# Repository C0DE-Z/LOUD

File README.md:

# Loud REV 1

A open source analog Video glitcher 

- Uses Karl Klomps Dirty Mixer
- Audio Reacitve Effects

- Check code branch for Source code,

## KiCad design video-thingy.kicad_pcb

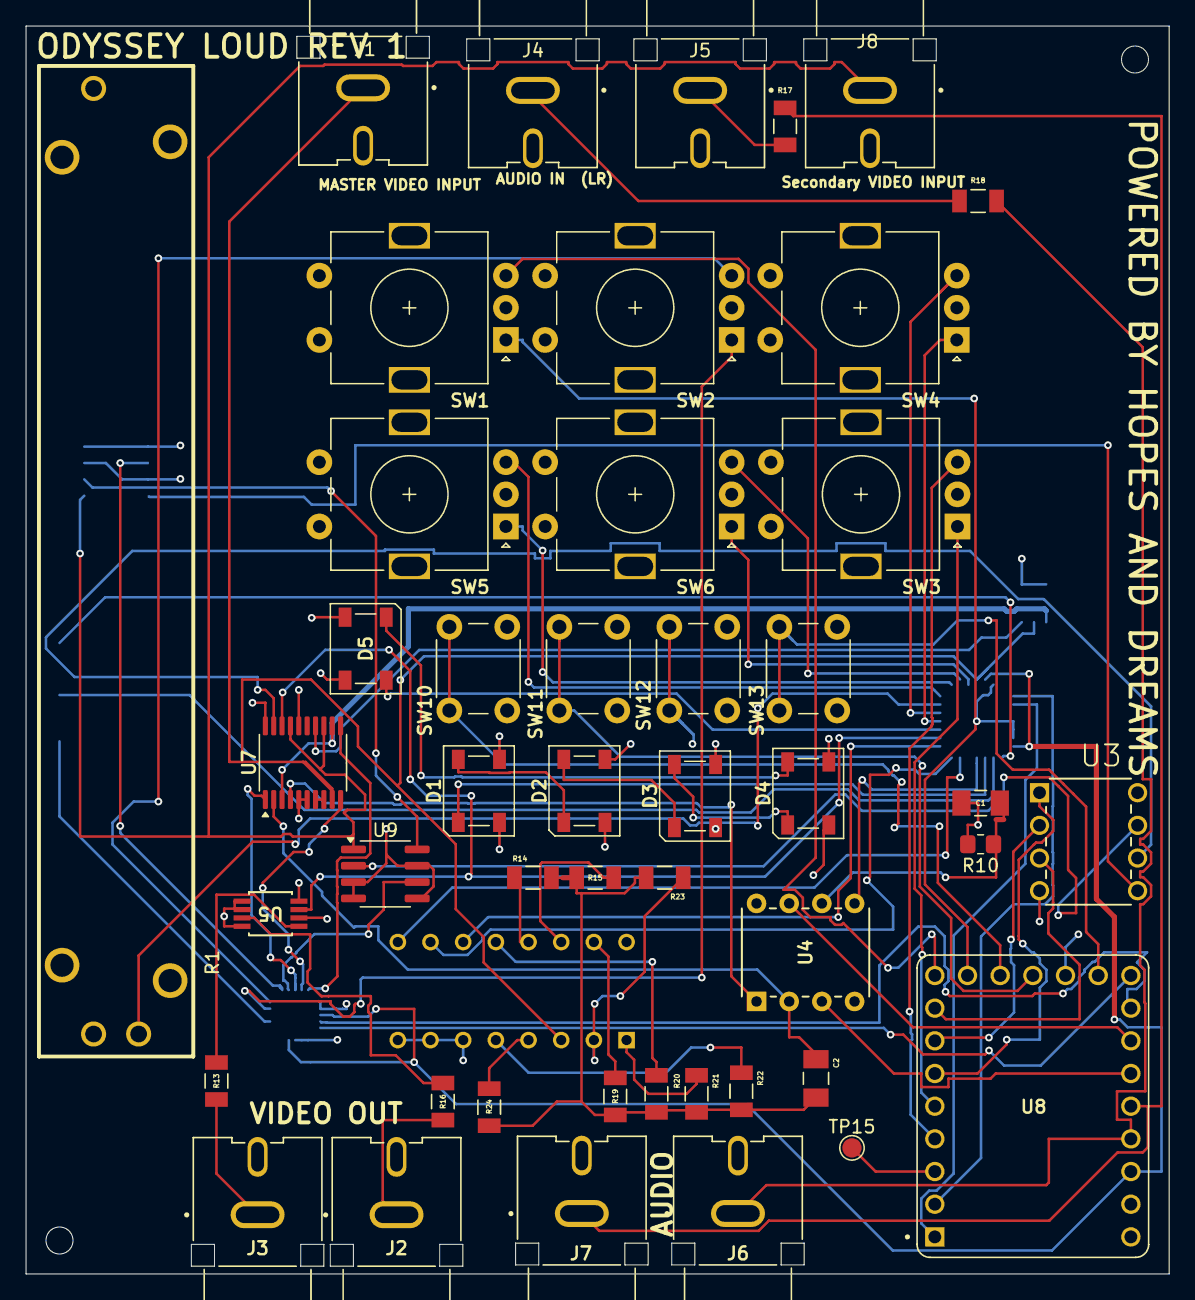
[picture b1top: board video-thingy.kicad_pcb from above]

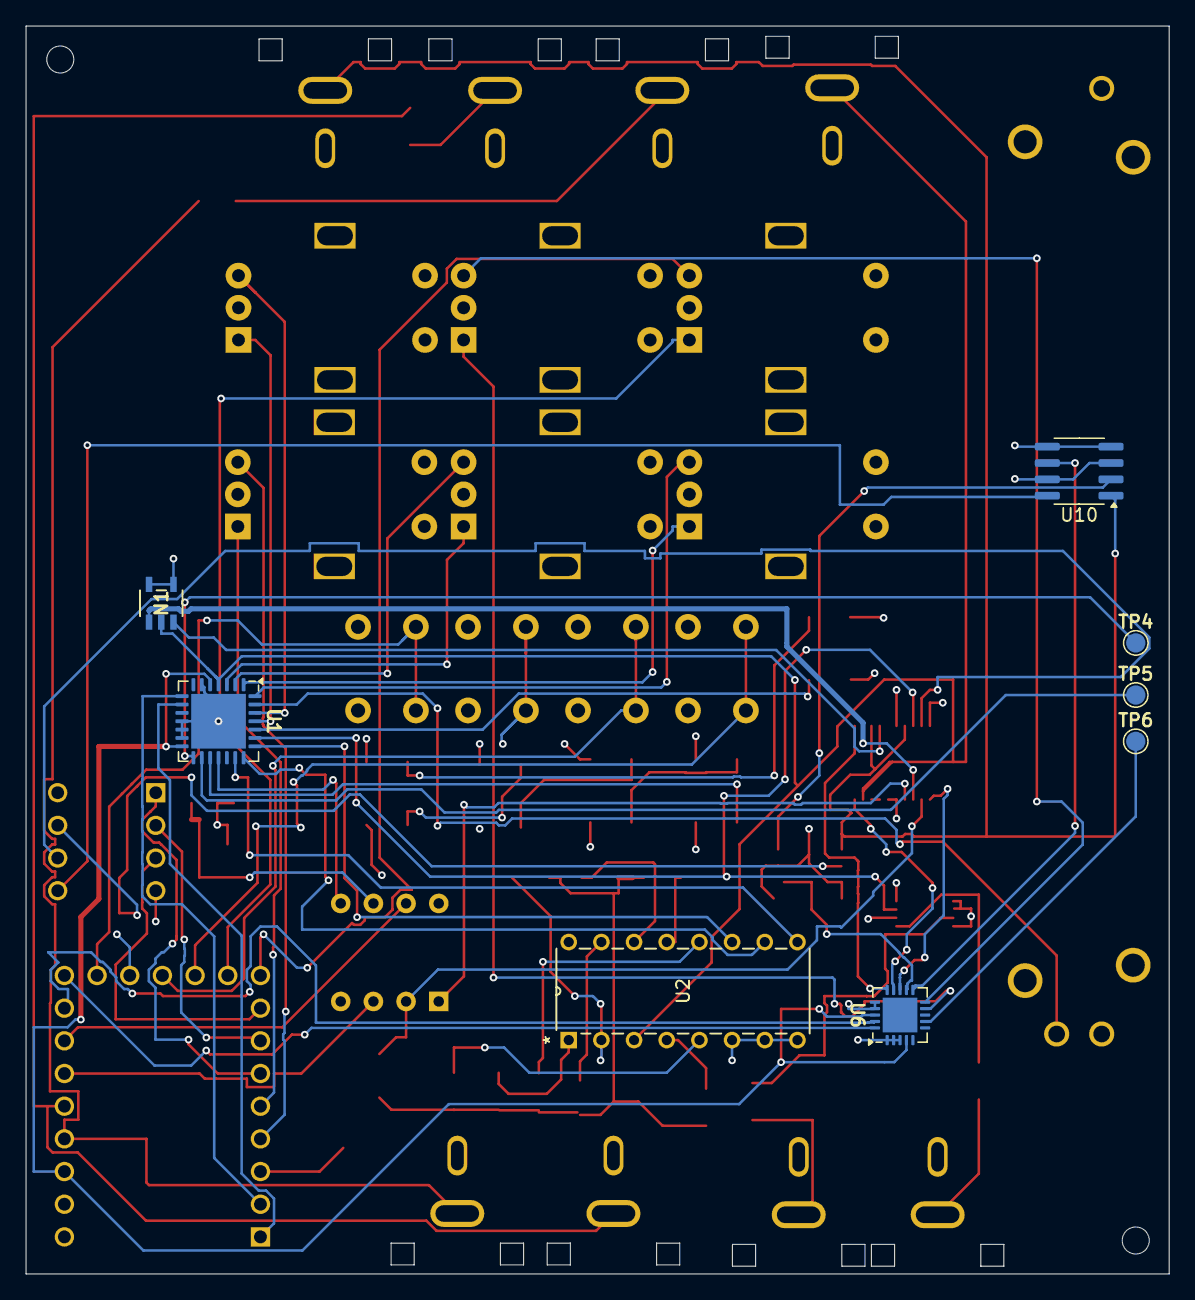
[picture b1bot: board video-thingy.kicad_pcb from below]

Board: 4 copper layers, 88.9 x 97.0 mm, 56 parts (8 on the bottom side), 74 nets.

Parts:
C1, C2: 0.1uF_0603_16V; CAPC3316X140N
D1, D2, D3, D4, D5: NeoPixel_THT; LED_Inolux_IN-PI554FCH_PLCC4_5.0x5.0mm_P3.2mm
J1, J2, J3, J4, J5, J6, J7, J8: RCJ-041; CUI_RCJ-041
MOUNT, MOUNT2: MountingHole_2.1mm
N1: DBV5-M
R1: PTA6043-2015DP-B103
R10: 680k; R_0805_2012Metric_Pad1.20x1.40mm_HandSolder
R13, R14, R15, R16, R17, R18, R19, R20, R21, R22, R23, R24: CRCW120675R0FKEAHP; RESC3116X65N
SW1, SW2, SW3, SW4, SW5, SW6: RotaryEncoder; RotaryEncoder_Alps_EC11E-Switch_Vertical_H20mm
SW10, SW11, SW12, SW13: Push_Button; SW_PUSH_6mm
TP4, TP5, TP6, TP15: TestPoint; TestPoint_Pad_D1.5mm
U1: MCP23017_ML; QFN-28-1EP_6x6mm_P0.65mm_EP4.25x4.25mm
U2: CD4051B; N16
U3: MCP41010; DIP254P762X432-8
U4: LM1881N; N08E_TEX
U5: MAX4392EUA_T; 21-0036_U8&plus_1_MXM
U6: MCP23008-xML; QFN-20-1EP_4x4mm_P0.5mm_EP2.7x2.7mm
U7: ADG734; TSSOP-20_4.4x6.5mm_P0.65mm
U8: RP2040-ZERO; MODULE_RP2040-ZERO
U9, U10: ADG419BR; SOIC-8_3.9x4.9mm_P1.27mm

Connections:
+3.3V: U1.5 (VDD), U1.14 (~RESET), U6.4 (~RESET), U6.18 (VDD), U8.21 (3V3)
A: SW4.A, U1.25 (GPB0)
A2: SW2.A, U6.9 (GP0)
A3: SW3.A, U8.5 (GP4)
A5: SW5.A, U1.1 (GPB4)
A6: SW6.A, U1.3 (GPB6)
AnalogL: J6.1, R18.1, U8.20 (GP29)
AnalogR: J7.1, R17.1, U8.19 (GP28)
AudioLIN: J4.1, R18.2
AudioRIN: J5.1, R17.2
B: SW4.B, U1.26 (GPB1)
B1: SW1.B, U8.9 (GP8)
B2: SW2.B, U6.10 (GP1)
B3: SW3.B, U8.4 (GP3)
B5: SW5.B, U1.28 (GPB3)
B6: SW6.B, U1.2 (GPB5)
BPOUT: U1.18 (GPA1), U4.5 (BPOUT)
Brightness: U1.23 (GPA6), U5.3 (INA+), U7.18
CLEAN: J1.1, N1.2 (B), U1.4 (GPB7), U2.3 (X), U7.9
CLEAN2: J8.1, U7.13, U7.17, U9.1, U10.1
CS: U3.1 (~CS), U8.6 (GP5)
CSOUT: U4.1 (CSOUT), U7.4
CVLN: C2.1, U4.2 (CVLN), U7.2
DIN: D5.4 (DIN), U1.24 (GPA7)
DOUT: D1.1 (DOUT), U1.17 (GPA0)
GND: C1.2, D1.2 (GND), D1.3 (VDD), D2.2 (GND), D2.3 (VDD), D3.2 (GND), D3.3 (VDD), D4.2 (GND), D4.3 (VDD), D5.2 (GND), D5.3 (VDD), J1.2, J2.2, J3.2, J4.2, J5.2, J6.2, J7.2, J8.2, N1.4 (+), N1.5 (-), R1.1, R1.3, R10.2, R22.1, SW1.A, SW1.C, SW2.C, SW3.C, SW4.C, SW5.C, SW6.C, SW10.2, SW11.2, SW12.1, SW12.2, SW13.2, U1.6 (VSS), U1.11 (A0), U1.12 (A1), U1.13 (A2), U1.29 (EP), U2.5 (X5), U2.6 (INH), U2.7 (VEE), U2.8 (VSS), U2.16 (VDD), U3.4 (VSS), U3.8 (VDD), U4.4 (GND), U4.8 (VCC), U5.2 (INA-), U5.4 (VEE), U5.5 (INB+), U5.6 (INB-), U5.8 (VCC), U6.1 (A2), U6.2 (A1), U6.3 (A0), U6.16 (GP7), U6.17 (VSS), U7.5 (VSS), U7.6 (GND), U7.16 (VDD), U7.20, U8.10 (GP9), U8.13 (GP12), U8.22 (GND), U8.23 (5V), U9.3 (GND), U9.4 (V+), U9.5 (VL), U9.7 (V-), U10.3 (GND), U10.4 (V+), U10.5 (VL), U10.7 (V-)
GP2-A: U6.11 (GP2), U10.6
GP3-A: U6.12 (GP3), U9.6
GP4-A: U6.13 (GP4), U7.1
GP5-A: U6.14 (GP5), U7.10
GP6-A: U6.15 (GP6), U7.11
GPA3: U1.20 (GPA3), U2.9 (C)
GPA4: U1.21 (GPA4), U2.10 (B)
GPA5: U1.22 (GPA5), U2.11 (A)
Gain: R1.2, U1.27 (GPB2)
MOSI: U3.3 (SI), U8.8 (GP7)
unnamed: C2.2, R14.2, R15.2, R19.2, R20.2, R21.2, R22.2, R23.2, R24.2
unnamed: D1.4 (DIN), D2.1 (DOUT)
unnamed: D2.4 (DIN), D3.1 (DOUT)
unnamed: D3.4 (DIN), D4.1 (DOUT)
unnamed: D4.4 (DIN), D5.1 (DOUT)
unnamed: TP5.1, U1.16 (INTA)
unnamed: TP4.1, U1.15 (INTB)
unnamed: R14.1, U2.13 (X0)
unnamed: R15.1, U2.14 (X1)
unnamed: R19.1, U2.15 (X2)
unnamed: R20.1, U2.12 (X3)
unnamed: R21.1, U2.1 (X4)
unnamed: R23.1, U2.2 (X6)
unnamed: R24.1, U2.4 (X7)
unnamed: U3.5 (PA0), U10.8
unnamed: U3.7 (PB0), U9.2
unnamed: R13.1, U5.1 (OUTA)
unnamed: R16.1, U5.7 (OUTB)
unnamed: TP6.1, U6.7 (INT)
unnamed: TP15.1, U8.3 (GP2)
unnamed: SW10.1, U8.11 (GP10)
unnamed: SW11.1, U8.12 (GP11)
unnamed: SW13.1, U8.14 (GP13)
unnamed: U9.8, U10.2
OEOUT: U4.7 (OEOUT), U8.17 (GP26)
PostProcessingMixed: U3.6 (PW0), U7.19
RSET: C1.1, R10.1, U4.6 (RSET)
SCK: U3.2 (SCK), U8.7 (GP6)
SCL: U1.8 (SCK), U8.2 (GP1)
SCL2: U6.19 (SCL), U8.16 (GP15)
SDA: U1.9 (SDA), U8.1 (GP0)
SDA2: U6.20 (SDA), U8.15 (GP14)
Sampler: N1.1 (A), U7.3, U7.12
VIDEOOUTA: J3.1, R13.2
VIDEOOUTB: J2.1, R16.2
VSOUT: U4.3 (VSOUT), U8.18 (GP27)
XOR: N1.3 (Y), U7.14
XORDOUT: U7.7, U7.8

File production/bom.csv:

Designator,Footprint,Quantity,Value,LCSC Part #
"C1, C2",CAPC3316X140N,2,0.1uF_0603_16V,
"D1, D2, D3, D4, D5",LED_Inolux_IN-PI554FCH_PLCC4_5.0x5.0mm_P3.2mm,5,NeoPixel_THT,
"J1, J2, J3, J4, J5, J6, J7, J8",CUI_RCJ-041,8,RCJ-041,
N1,DBV5-M,1,~,
R1,PTA6043-2015DP-B103,1,PTA6043-2015DP-B103,
R10,0805,1,680k,
"R13, R14, R15, R16, R17, R18, R19, R20, R21, R22, R23, R24",RESC3116X65N,12,CRCW120675R0FKEAHP,
"SW1, SW2, SW3, SW4, SW5, SW6",RotaryEncoder_Alps_EC11E-Switch_Vertical_H20mm,6,RotaryEncoder,
"SW10, SW11, SW12, SW13",SW_PUSH_6mm,4,Push_Button,
"TP15, TP4, TP5, TP6",TestPoint_Pad_D1.5mm,4,TestPoint,
U1,QFN-28-1EP_6x6mm_P0.65mm_EP4.25x4.25mm,1,MCP23017_ML,
"U10, U9",SOIC-8_3.9x4.9mm_P1.27mm,2,ADG419BR,
U2,N16,1,CD4051B,
U3,DIP254P762X432-8,1,MCP41010,
U4,N08E_TEX,1,LM1881N,
U5,21-0036_U8&plus_1_MXM,1,MAX4392EUA_T,
U6,QFN-20-1EP_4x4mm_P0.5mm_EP2.7x2.7mm,1,MCP23008-xML,
U7,TSSOP-20_4.4x6.5mm_P0.65mm,1,ADG734,
U8,MODULE_RP2040-ZERO,1,RP2040-ZERO,

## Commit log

2025-05-22 Init
2025-05-23 Update pcb, for prod
2025-05-24 Routing optimization
2025-05-24 Routing opti
2025-06-24 Create LICENSE
2025-06-24 Update LICENSE
